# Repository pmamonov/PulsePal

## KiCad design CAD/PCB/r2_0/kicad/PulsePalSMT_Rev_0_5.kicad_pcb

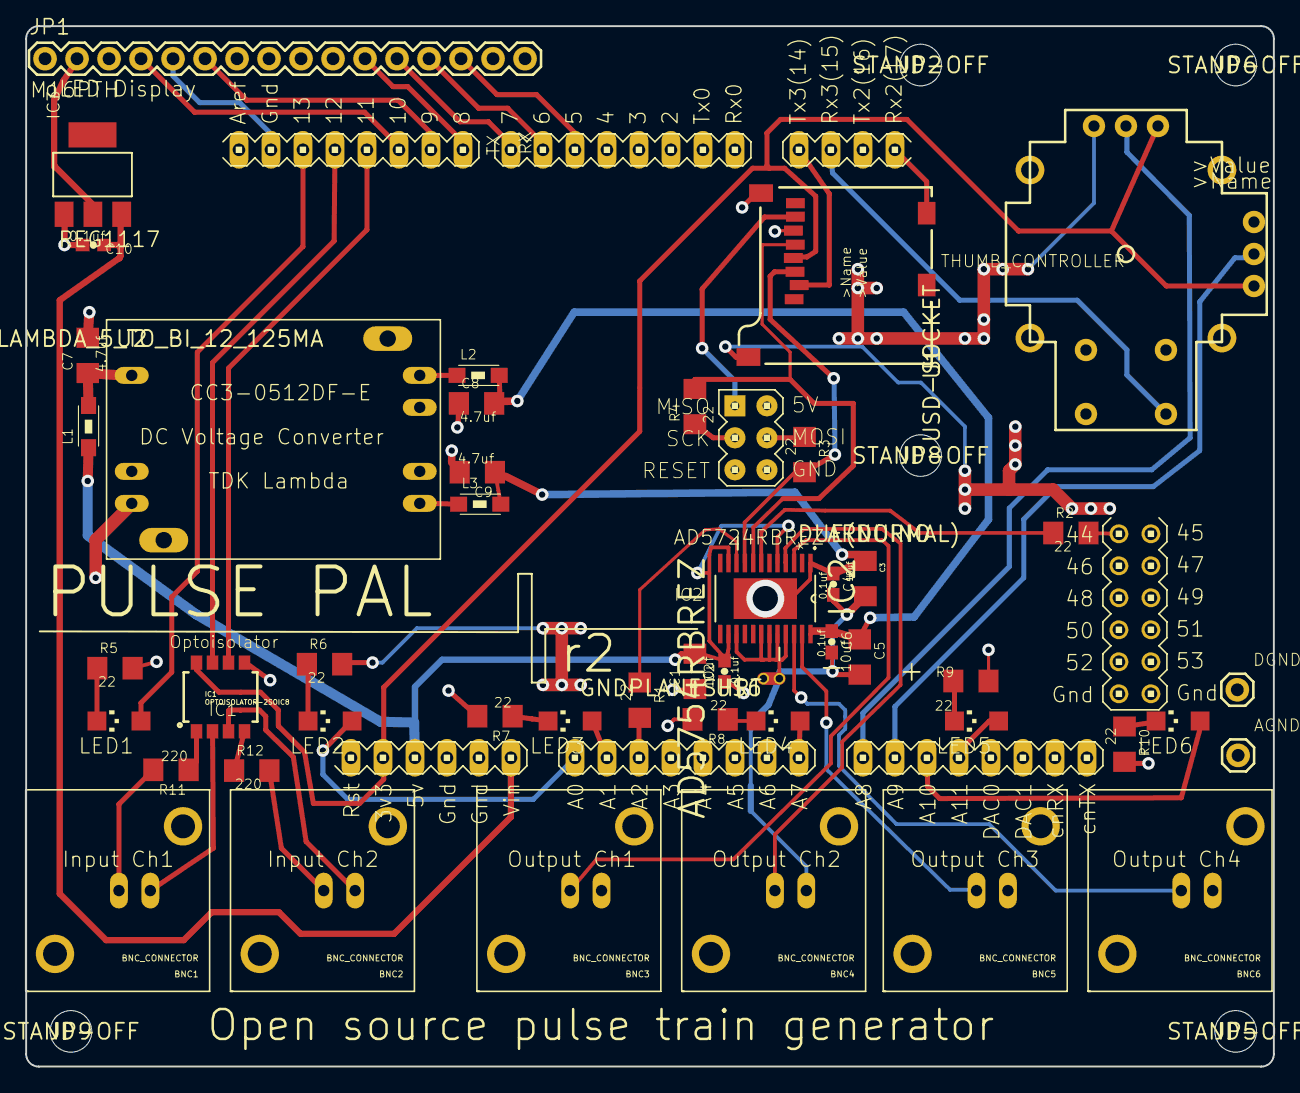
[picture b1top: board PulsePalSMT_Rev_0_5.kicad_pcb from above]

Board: 4 copper layers, 99.0 x 82.6 mm, 53 parts (0 on the bottom side), 55 nets.

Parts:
AGND: 1X01
ARDUINO: DUE(NORMAL)
BNC1, BNC2, BNC3, BNC4, BNC5, BNC6: BNC_CONNECTOR
C1, C3, C5: 10uf; 1206
C2, C4, C6, C10: 0.1uf; 0603-CAP
C7, C8, C9: 4.7uf; 1206
DGND: 1X01
IC1: OPTOISOLATOR-2SOIC8; SO08-2
IC2: AD5754RBREZ; SOP65P640X120-25N
IC3: REG1117; SOT223
JP1: M16PTH; 1X16
JP2, JP5, JP6, JP8, JP9: STAND-OFF
L1, L2, L3: 1206
LED1, LED2, LED3, LED4, LED5, LED6: CHIPLED_1206
R1, R2, R3, R4, R5, R6, R7, R8, R9, R10: 22; 1206
R11, R12: 220; 1206
THUMB_CONTROLLER: JOYSTICK
U1: USD-SOCKET; MICROSD_1%3a1
U2: TDK_LAMBDA_5_TO_BI_12_125MA
U$6: GNDPLANESHRT

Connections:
5V: ARDUINO.5V, C1.2, C2.2, IC2.5, IC2.11, IC2.14, L1.1
AGND: AGND.1, BNC3.GND, BNC4.GND, BNC5.GND, BNC6.GND, C3.2, C4.2, C5.2, C6.2, IC2.15, IC2.18, IC2.19, IC2.20, IC2.21, U$6.AGND
GND: ARDUINO.GND1, ARDUINO.GND_, C1.1, C2.1, C7.2, C8.1, C9.2, C10.2, DGND.1, IC1.5, IC3.1, JP1.1, JP1.5, R5.2, R6.2, R7.2, R8.2, R9.2, R10.2, THUMB_CONTROLLER.B2A, THUMB_CONTROLLER.H3, THUMB_CONTROLLER.V3, U1.6, U1.GND1, U1.GND3, U2.P$2, U2.P$3, U2.P$5, U$6.GND
H_NAV: ARDUINO.VIN, C10.1, IC3.3
LED2: ARDUINO.A0, LED2.A
LED3: ARDUINO.A1, LED3.A
LED4: ARDUINO.A7, LED4.A
LED5: ARDUINO.A11, LED5.A
LED6: ARDUINO.A10, LED6.A
MISO1: ARDUINO.MISO, U1.7
unnamed: L2.1, U2.P$7
unnamed: L3.1, U2.P$4
unnamed: BNC3.SIGN, IC2.3
unnamed: BNC4.SIGN, IC2.4
unnamed: BNC5.SIGN, IC2.23
unnamed: BNC6.SIGN, IC2.22
unnamed: BNC1.GND, IC1.2
unnamed: BNC1.SIGN, R11.2
unnamed: BNC2.GND, IC1.3
unnamed: BNC2.SIGN, R12.2
unnamed: ARDUINO.SCK, R4.1
unnamed: ARDUINO.MOSI, R3.1
unnamed: ARDUINO.44, R2.2
unnamed: ARDUINO.A2, R1.2
unnamed: IC2.7, R2.1
unnamed: IC2.10, R1.1
unnamed: ARDUINO.RX3, THUMB_CONTROLLER.B1A
unnamed: ARDUINO.11, IC1.6
unnamed: LED1.C, R5.1
unnamed: LED2.C, R6.1
unnamed: LED3.C, R7.1
unnamed: LED4.C, R8.1
unnamed: LED5.C, R9.1
unnamed: LED6.C, R10.1
unnamed: IC1.1, R11.1
unnamed: IC3.2, JP1.2
unnamed: ARDUINO.12, IC1.7
unnamed: ARDUINO.5, JP1.14
unnamed: ARDUINO.13, LED1.A
unnamed: ARDUINO.10, JP1.4
unnamed: ARDUINO.9, JP1.6
unnamed: ARDUINO.8, JP1.11
unnamed: ARDUINO.7, JP1.12
unnamed: ARDUINO.6, JP1.13
unnamed: IC1.4, R12.1
unnamed: ARDUINO.A8, THUMB_CONTROLLER.H2
unnamed: C5.1, C6.1, C8.2, IC2.24, L2.2
unnamed: C3.1, C4.1, C9.1, IC2.1, IC2.25, L3.2
unnamed: C7.1, L1.2, U2.P$1
unnamed: ARDUINO.A9, THUMB_CONTROLLER.V2
ROMLOAD: ARDUINO.TX3, U1.2
SCK1: IC2.8, R4.2, U1.5
SDA1: IC2.9, R3.2, U1.3
VCC: ARDUINO.3V3, IC1.8, THUMB_CONTROLLER.H1, THUMB_CONTROLLER.V1, U1.4
V_NAV: ARDUINO.RX2, U1.CD1

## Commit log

2017-06-01 add .gitignore
2017-06-01 Python/PulsePalExample.py: use /dev/ttyACM0 for serial port
2017-06-02 debug: firmware: 2.0.1: add blinks
2017-06-02 firmware: 2.0.1: add dependencies
2017-06-02 firmware: 2.0.1: add Makefile
2017-06-02 firmware: 2.0.1: fix missing function declarations
2017-06-03 FIXME: PCB/r2_0: convert to kicad
2017-06-04 PCB/r2_0/kicad: 2 layer PCB
2017-06-05 firmware: 2.0.1: don't hang on SD card failure
2017-06-05 Python: remove PulsePal.pyc
2017-06-05 Revert "debug: firmware: 2.0.1: add blinks"
    This reverts commit 436b49206fa35a8956abfd631d87321b70a2f7d2.
    Conflicts:
    Firmware/PulsePal_2_0_1/PulsePal_2_0_1.ino
2017-12-15 debug: firmware: 2.0.1: add blinks and disable timer
    This reverts commit f85ee5d55dc8ef27b64c639d329a0b08c6103d6d.
2017-12-16 Revert "debug: firmware: 2.0.1: add blinks and disable timer"
    This reverts commit 8af6618222c992525e9ac101a1f1a49bec92fb7c.
2018-03-08 add support for analog readings (A8)
